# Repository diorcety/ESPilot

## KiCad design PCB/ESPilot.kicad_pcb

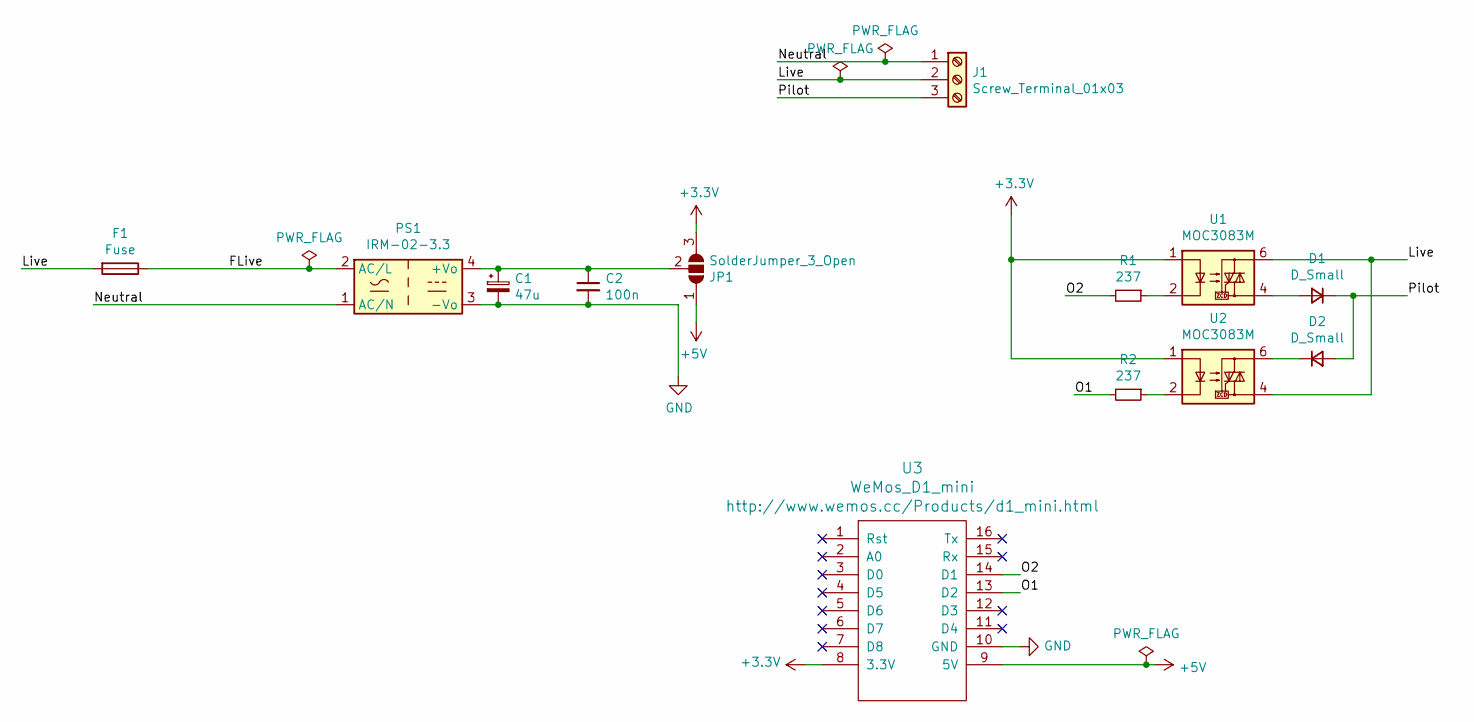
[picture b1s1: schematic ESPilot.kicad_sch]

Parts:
C1: 47u; CP_Radial_D5.0mm_P2.00mm
C2: 100n; C_Rect_L7.0mm_W3.5mm_P2.50mm_P5.00mm
D1, D2: D_Small; D_DO-35_SOD27_P10.16mm_Horizontal
F1: Fuse; Fuseholder_TR5_Littelfuse_No560_No460
J1: Screw_Terminal_01x03; TerminalBlock_bornier-3_P5.08mm
JP1: SolderJumper_3_Open; SolderJumper-3_P2.0mm_Open_TrianglePad1.0x1.5mm
PS1: IRM-02-3.3; Converter_ACDC_MeanWell_IRM-02-xx_THT
R1, R2: 237; R_Axial_DIN0207_L6.3mm_D2.5mm_P10.16mm_Horizontal
U1, U2: MOC3083M; DIP-5-6_W7.62mm
U3: WeMos_D1_mini; wemos-d1-mini-with-pin-header-and-connector

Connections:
+3V3: JP1.3 (B), U1.1, U2.1, U3.8 (3.3V)
+5V: JP1.1 (A), U3.9 (5V)
/FLive: F1.1, PS1.2 (AC/L)
/Live: F1.2, J1.2, U1.6, U2.4
/Neutral: J1.1, PS1.1 (AC/N)
/O1: R2.2, U3.13 (D2)
/O2: R1.2, U3.14 (D1)
/Pilot: D1.1 (K), D2.2 (A), J1.3
GND: C1.2, C2.2, PS1.3 (-Vo), U3.10 (GND)
unnamed: C1.1, C2.1, JP1.2 (C), PS1.4 (+Vo)
unnamed: D1.2 (A), U1.4
unnamed: D2.1 (K), U2.6
unnamed: R1.1, U1.2
unnamed: R2.1, U2.2

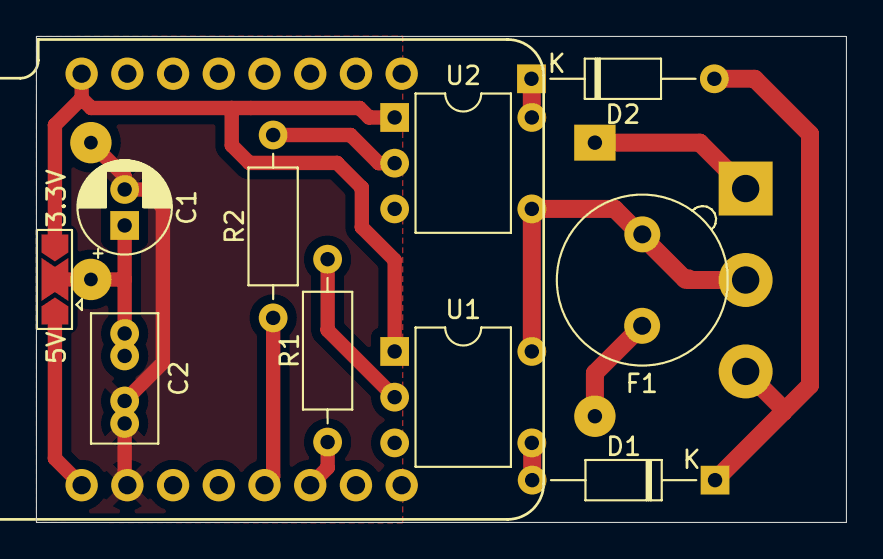
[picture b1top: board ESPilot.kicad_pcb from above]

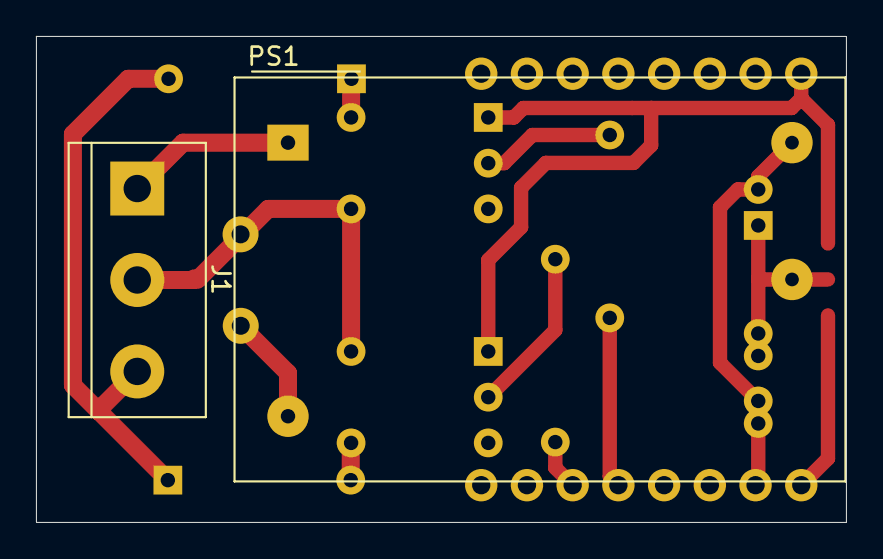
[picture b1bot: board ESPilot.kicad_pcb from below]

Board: 2 copper layers, 45.0 x 27.0 mm, 13 parts (2 on the bottom side), 14 nets.

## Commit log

2026-02-09 esphome: Upgrade to 2025.11.2
